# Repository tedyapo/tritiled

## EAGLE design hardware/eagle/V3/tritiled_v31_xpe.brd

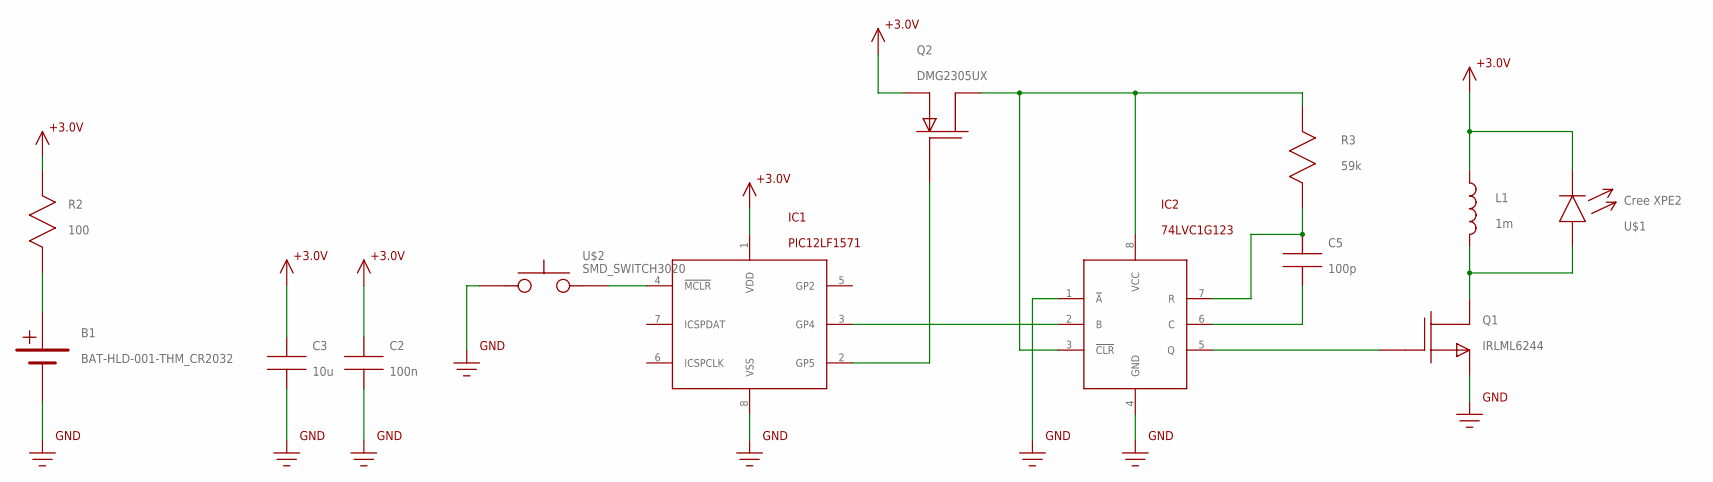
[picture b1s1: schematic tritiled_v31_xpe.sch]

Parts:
B1: BAT-HLD-001-THM_CR2032; CR2032_BAT-HLD-001-THM
C2: 100n; 0805
C3: 10u; 1206
C5: 100p; C0603
IC1: PIC12LF1571; SOIC8
IC2: 74LVC1G123; SM8
L1: 1m; SRR6028_INDUCTOR
Q1: IRLML6244; SOT-23
Q2: DMG2305UX; SOT-23
R2: 100; R1206
R3: 59k; R0603
U$1: Cree XPE2; CREE_XPE_LED
U$2: SMD_SWITCH3020; SWITCH_3020

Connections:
+3.6V: C2.P$1, C3.P$1, IC1.1 (VDD), L1.P$1 (1), Q2.2 (S), R2.P$1, U$1.C
GND: B1.GND (0V), C2.P$2, C3.P$2, IC1.8 (VSS), IC2.1 (!A!), IC2.4 (GND), Q1.2 (S), U$2.A
unnamed: C5.P$1, IC2.7 (R), R3.P$1
unnamed: IC2.5 (Q), Q1.1 (G)
unnamed: IC1.2 (GP5), Q2.1 (G)
unnamed: IC1.3 (GP4), IC2.2 (B)
unnamed: C5.P$2, IC2.6 (C)
unnamed: IC1.4 (!MCLR!), U$2.B
unnamed: IC2.3 (!CLR!), IC2.8 (VCC), Q2.3 (D), R3.P$2
unnamed: B1.+V@1 (+V), B1.+V@2 (+V), B1.+V@3 (+V), B1.+V@4 (+V), R2.P$2
unnamed: L1.P$2 (2), Q1.3 (D), U$1.A

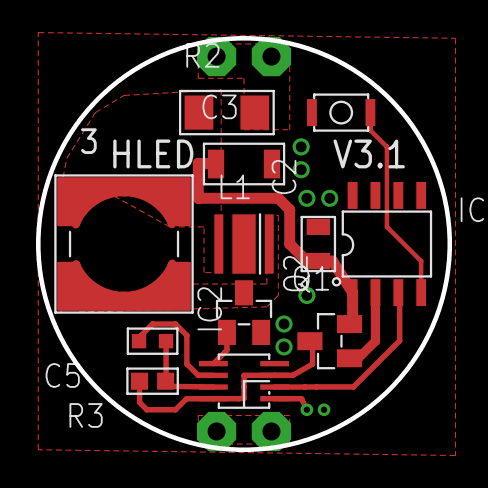
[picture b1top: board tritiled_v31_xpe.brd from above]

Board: 2 copper layers, 22.9 x 22.9 mm, 13 parts (1 on the bottom side), 11 nets.

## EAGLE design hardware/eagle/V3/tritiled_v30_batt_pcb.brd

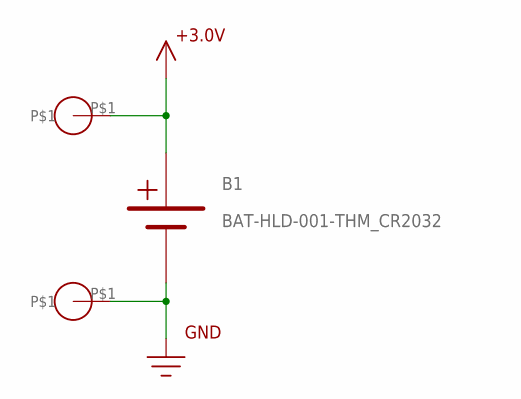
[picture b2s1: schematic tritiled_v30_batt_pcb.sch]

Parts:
B1: BAT-HLD-001-THM_CR2032; CR2032_BAT-HLD-001-THM
U$1, U$2: HDR_1_PIN

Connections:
+3.6V: B1.+V@1 (+V), B1.+V@2 (+V), B1.+V@3 (+V), B1.+V@4 (+V), U$1.P$1
GND: B1.GND (0V), U$2.P$1

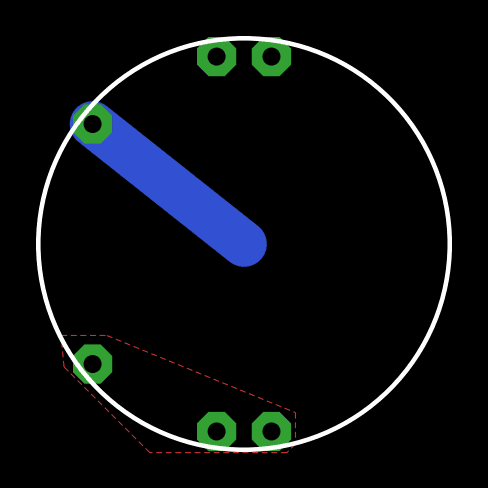
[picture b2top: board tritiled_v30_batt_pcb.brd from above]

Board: 2 copper layers, 22.9 x 22.9 mm, 3 parts (1 on the bottom side), 2 nets.

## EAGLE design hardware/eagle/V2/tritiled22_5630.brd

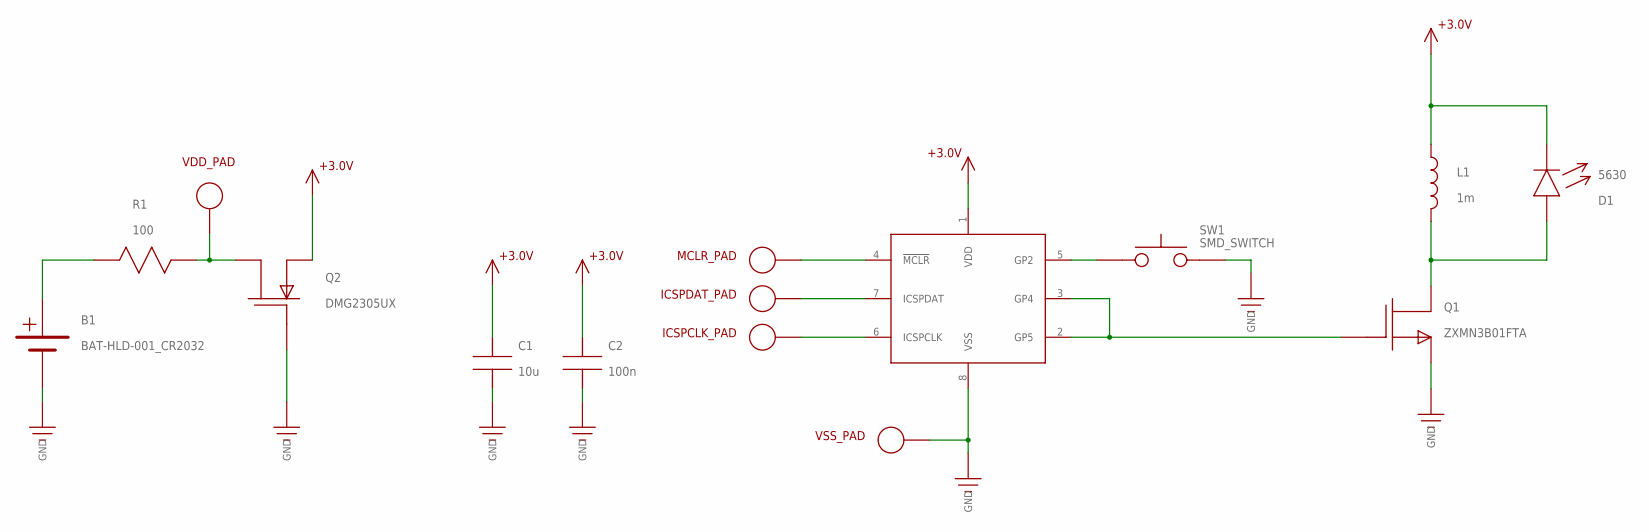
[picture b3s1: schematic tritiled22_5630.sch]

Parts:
B1: BAT-HLD-001_CR2032; CR2032_BAT-HLD_001
C1: 10u; 1206
C2: 100n; 0805
D1: 5630; LED_5630
ICSPCLK_PAD: ICSP_PAD
ICSPDAT_PAD: ICSP_PAD
L1: 1m; SRR6028_INDUCTOR
MCLR_PAD: ICSP_PAD
Q1: ZXMN3B01FTA; SOT-23
Q2: DMG2305UX; SOT-23
R1: 100; R1206
SW1: SMD_SWITCH
U1: PIC12LF1571; SOIC8
VDD_PAD: ICSP_PAD
VSS_PAD: ICSP_PAD

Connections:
+3.3V: C1.P$1, C2.P$1, D1.C@1 (C), D1.C@2 (C), L1.P$1 (1), Q2.2 (S), U1.1 (VDD)
GND: B1.GND (0V), C1.P$2, C2.P$2, Q1.2 (S), Q2.1 (G), SW1.P$3, SW1.P$4, U1.8 (VSS), VSS_PAD.P$2
unnamed: MCLR_PAD.P$2, U1.4 (!MCLR!)
unnamed: ICSPDAT_PAD.P$2, U1.7 (ICSPDAT)
unnamed: ICSPCLK_PAD.P$2, U1.6 (ICSPCLK)
unnamed: D1.A@1 (A), D1.A@2 (A), L1.P$2 (2), Q1.3 (D)
unnamed: SW1.P$1, SW1.P$2, U1.5 (GP2)
unnamed: Q1.1 (G), U1.2 (GP5), U1.3 (GP4)
VBATT: B1.+V1 (+V), B1.+V2 (+V), R1.P$1
VSAFE: Q2.3 (D), R1.P$2, VDD_PAD.P$2

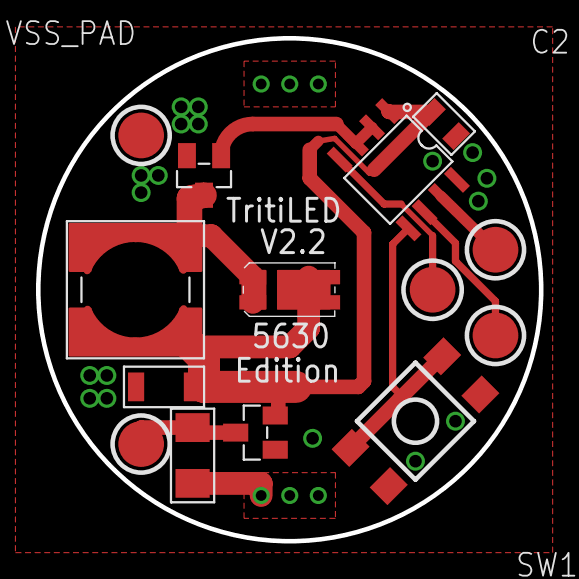
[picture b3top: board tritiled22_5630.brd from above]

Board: 2 copper layers, 27.9 x 27.9 mm, 15 parts (1 on the bottom side), 10 nets.

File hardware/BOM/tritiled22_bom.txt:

(1) PIC12LF1571 8-SOIC 
      DigiKey part # PIC12LF1571-I/SN-ND $0.57 each
(1) Wurth 744062102 1mH inductor
      DigiKey part # 732-3676-1-ND $1.57 each
(1) 10uF 25V 1206 X7R MLCC capacitor
      DigiKey part # 1276-1804-1-ND $0.26 each
(1) 0.1uF 25V 0805 X7R MLCC capacitor
      DigiKey part #311-1141-1-ND $0.10 each
(1) 100 ohm 1206 resistor
      DigiKey part # 311-100FRCT-ND $0.10 each
(1) ZXMN3B01FTA N-channel SOT23 MOSFET
      DigiKey part # ZXMN3B01FCT-ND $0.60 each
(1) DMG2305UX P-channel SOT23 MOSFET
      DigiKey part # DMG2305UX-13DICT-ND $0.44 each
(1) CR2032 Battery retainer
      Digikey part # BK-912-G-TR $0.63 each
(1) Switch E-Switch #TL3305BF260QG
      Digikey part # EG5354CT-ND $0.21 each
(1) CHANZON 3W LED (cyan is best).
    Find them on Amazon : $9.52/10, AliExpress : $7.90/10, or Ebay (various sellers/prices)
(1) PCB. Order from OSH Park. $6.15 for 3.

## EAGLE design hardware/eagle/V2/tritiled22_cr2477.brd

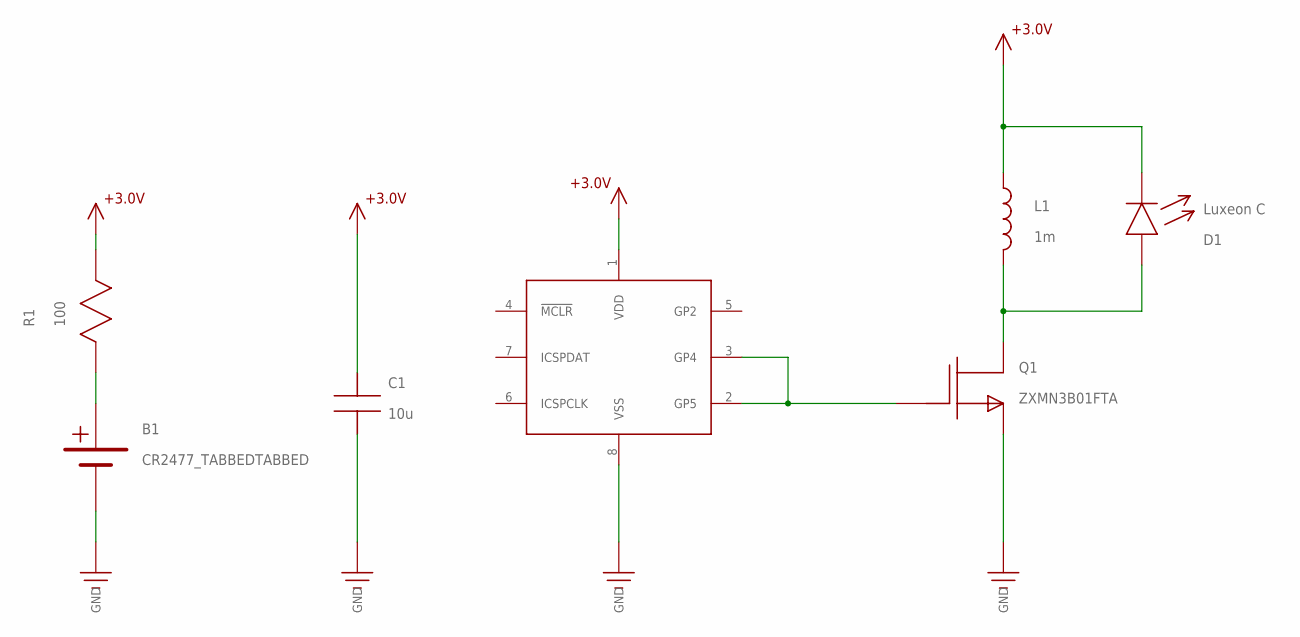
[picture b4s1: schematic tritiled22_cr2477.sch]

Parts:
B1: CR2477_TABBEDTABBED; CR2477_TABBED
C1: 10u; 1206
D1: Luxeon C; LUXEON_C
L1: 1m; SRR6028_INDUCTOR
Q1: ZXMN3B01FTA; SOT-23
R1: 100; R1206
U1: PIC12LF1571; SOIC8

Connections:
+3.3V: C1.P$1, D1.C, L1.P$1 (1), R1.P$2, U1.1 (VDD)
GND: B1.GND (0V), C1.P$2, Q1.2 (S), U1.8 (VSS)
unnamed: D1.A, L1.P$2 (2), Q1.3 (D)
unnamed: Q1.1 (G), U1.2 (GP5), U1.3 (GP4)
VBATT: B1.+3V (+V), R1.P$1

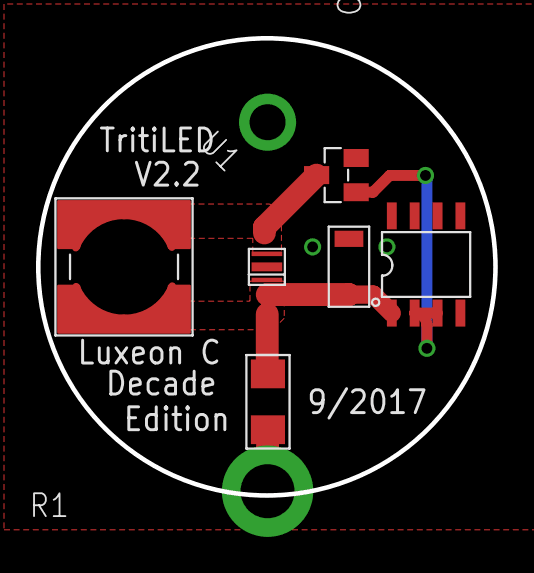
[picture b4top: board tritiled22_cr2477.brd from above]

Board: 2 copper layers, 25.4 x 25.4 mm, 7 parts (1 on the bottom side), 5 nets.

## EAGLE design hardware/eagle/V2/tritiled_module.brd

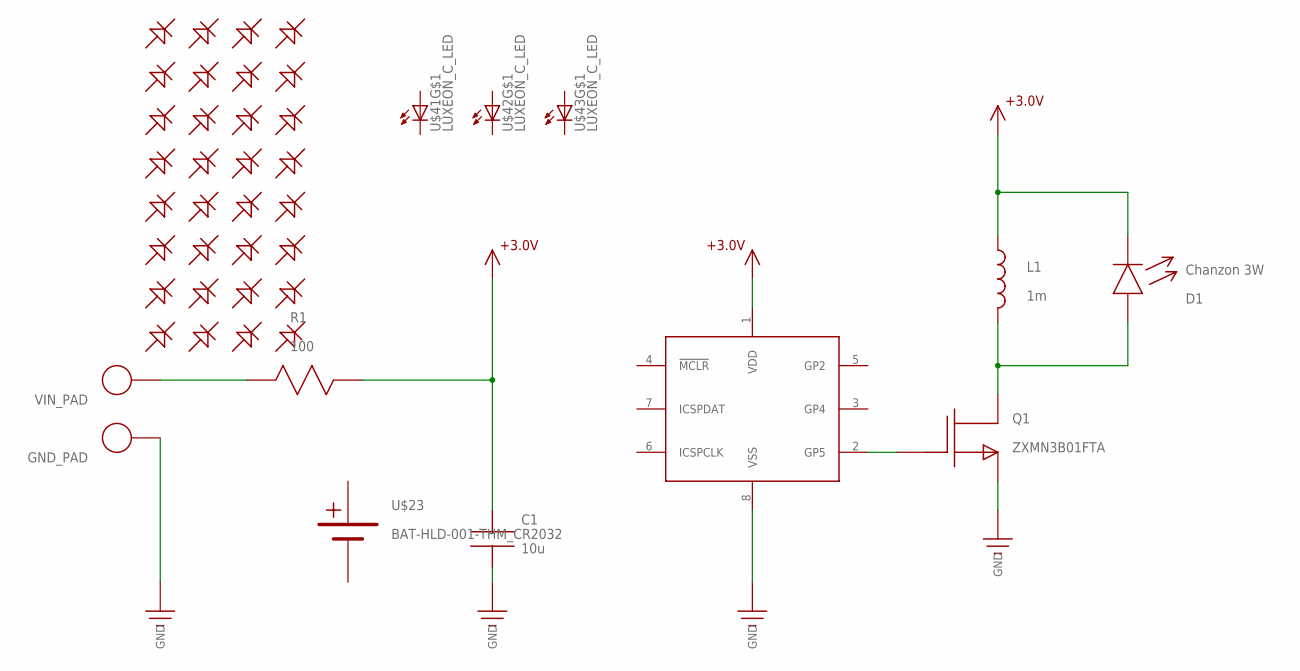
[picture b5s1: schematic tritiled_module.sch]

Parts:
C1: 10u; 1206
D1: Chanzon 3W; LED_3W
GND_PAD: ICSP_PAD
L1: 1m; SRR6028_INDUCTOR
Q1: ZXMN3B01FTA; SOT-23
R1: 100; R1206
U1: PIC12LF1571; SOIC8
U$1, U$5, U$6, U$7, U$8, U$9, U$10, U$12, U$16, U$17, U$18, U$19, U$20, U$21, U$22, U$24, U$25, U$26, U$27, U$28, U$29, U$30, U$31, U$32, U$33, U$34, U$35, U$36, U$37, U$38, U$39, U$40: LED_0603
U$23: BAT-HLD-001-THM_CR2032; CR2032_BAT-HLD-001-THM
U$41, U$42, U$43: LUXEON_C_LED; LUXEON_C
VIN_PAD: ICSP_PAD

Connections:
0V: U$23.GND (0V)
+3V: C1.P$1, D1.C, L1.P$1 (1), R1.P$2, U1.1 (VDD)
+V: U$23.+V@1 (+V), U$23.+V@2 (+V), U$23.+V@3 (+V), U$23.+V@4 (+V)
GND: C1.P$2, GND_PAD.P$2, Q1.2 (S), U1.8 (VSS)
unnamed: R1.P$1, VIN_PAD.P$2
unnamed: D1.A, L1.P$2 (2), Q1.3 (D)
unnamed: Q1.1 (G), U1.2 (GP5)

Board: 2 copper layers, 44 parts (4 on the bottom side), 6 nets, no tracks yet.

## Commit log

2017-07-12 initial commit for v22
2017-07-12 added design files for 3D printed case for V2.x series boards
2017-07-13 added names and values to schematic and PCB
2017-07-13 added images to docs dir
2017-07-13 more images
2017-07-13 added BOM for v2.2, library tweaks
2017-07-16 modified library and tritiled22 PCB for solder stencil generation
2017-07-27 changed default pulses from 1 to 2 for 2.5 year run-time (was 3+ years)
2017-08-16 Added new LED eiditons: 5630, Luxeon C, Luxeon Z fixed inconsistent C2 value: now should be 100n everywhere
2017-08-17 added Cree XP-E(2) edition
2017-08-20 added PCBs for CR2354-based versions
2017-08-28 added new reversed editions
2017-11-07 added "normal brightness" source/hex for "nobutton" versions
2017-12-18 added V3.0; re-arranged directory structure
2017-12-21 Set theme jekyll-theme-midnight
2017-12-23 Fixed V3.0 board (74LVC1G123 A_bar now pulled low)
2017-12-27 Smaller v30 boards to got 5g (possibly 3g) polystyrene jars with new LED types
2017-12-30 added luxeon_c V30 boards (normal plus reverse)
2018-01-03 updated files for initial V3.0 release
2018-01-04 correct values for R3
2018-01-04 added image of V3
2018-01-06 added c-source for V3.0 selectable runtime
2018-01-06 revised C code for V3.0
2018-01-06 added calibrated values to V3.0 C-code
2018-01-07 fixe bug with writing HEF too often
2018-01-09 Added PCB designs for V31 - includes mode switch
2018-01-09 V3.1 silkscreen says "V3.1"
2018-01-12 fixed debounce issues
2018-01-13 added preview of brightness to power-on configuration UI
2018-01-13 Update LICENSE
2018-01-14 removed expensive % operator to save instructions
2018-01-23 added code for V3.x calibration
2023-06-04 interactive BOM and additional calibration plots
2023-06-04 added interactive BOMs for v31 and v30
